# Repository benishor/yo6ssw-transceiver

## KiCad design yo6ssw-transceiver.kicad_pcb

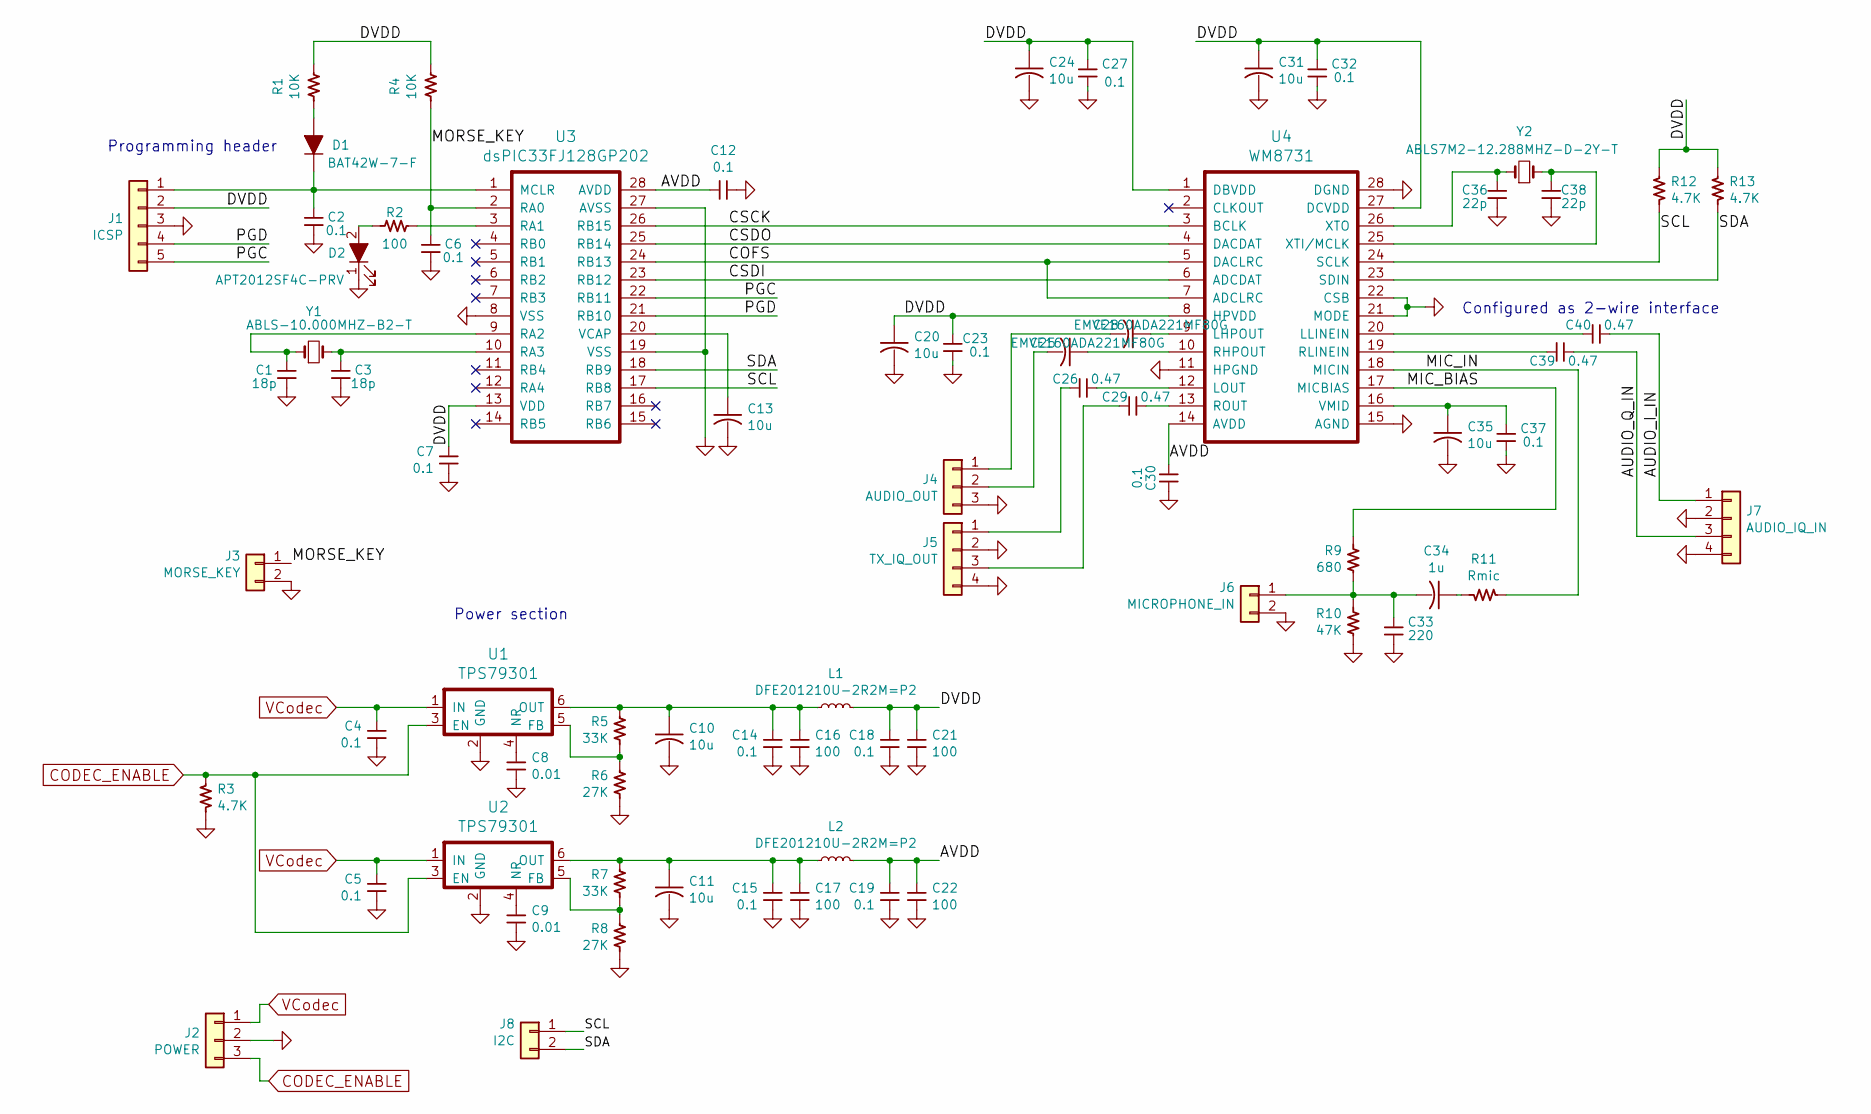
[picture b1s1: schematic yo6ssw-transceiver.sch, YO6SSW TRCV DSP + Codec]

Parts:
C1, C3: 18p; C_0805_2012Metric_Pad1.15x1.50mm_HandSolder
C2, C4, C5, C6, C7, C12, C14, C15, C18, C19, C23, C27, C30, C32, C37: 0.1; C_0805_2012Metric_Pad1.15x1.50mm_HandSolder
C8, C9: 0.01; C_0805_2012Metric_Pad1.15x1.50mm_HandSolder
C10, C11, C13, C20, C24, C31, C35: 10u; C_0805_2012Metric_Pad1.15x1.50mm_HandSolder
C16, C17, C21, C22: 100; C_0805_2012Metric_Pad1.15x1.50mm_HandSolder
C25, C28: EMVE160ADA221MF80G; CP_Elec_6.3x7.7
C26, C29, C39, C40: 0.47; C_0805_2012Metric_Pad1.15x1.50mm_HandSolder
C33: 220; C_0805_2012Metric_Pad1.15x1.50mm_HandSolder
C34: 1u; C_0805_2012Metric_Pad1.15x1.50mm_HandSolder
C36, C38: 22p; C_0805_2012Metric_Pad1.15x1.50mm_HandSolder
D1: BAT42W-7-F; D_SOD-123
D2: APT2012SF4C-PRV; D_0805_2012Metric_Pad0.97x1.50mm_HandSolder
J1: ICSP; PinSocket_1x05_P2.54mm_Vertical_SMD_Pin1Left
J2: POWER; PinSocket_1x03_P2.54mm_Vertical_SMD_Pin1Left
J3: MORSE_KEY; PinSocket_1x02_P2.54mm_Vertical_SMD_Pin1Left
J4: AUDIO_OUT; PinSocket_1x03_P2.54mm_Vertical_SMD_Pin1Left
J5: TX_IQ_OUT; PinSocket_1x04_P2.54mm_Vertical_SMD_Pin1Left
J6: MICROPHONE_IN; PinSocket_1x02_P2.54mm_Vertical_SMD_Pin1Left
J7: AUDIO_IQ_IN; PinSocket_1x04_P2.54mm_Vertical_SMD_Pin1Left
J8: I2C; PinSocket_1x02_P2.54mm_Vertical_SMD_Pin1Left
L1, L2: DFE201210U-2R2M=P2; L_0805_2012Metric_Pad1.15x1.50mm_HandSolder
R1, R4: 10K; R_0805_2012Metric_Pad1.15x1.50mm_HandSolder
R2: 100; R_0805_2012Metric_Pad1.15x1.50mm_HandSolder
R3, R12, R13: 4.7K; R_0805_2012Metric_Pad1.15x1.50mm_HandSolder
R5, R7: 33K; R_0805_2012Metric_Pad1.15x1.50mm_HandSolder
R6, R8: 27K; R_0805_2012Metric_Pad1.15x1.50mm_HandSolder
R9: 680; R_0805_2012Metric_Pad1.15x1.50mm_HandSolder
R10: 47K; R_0805_2012Metric_Pad1.15x1.50mm_HandSolder
R11: Rmic; R_0805_2012Metric_Pad1.15x1.50mm_HandSolder
U1, U2: TPS79301; SOT-23-6_Handsoldering
U3: dsPIC33FJ128GP202; SOIC-28W_7.5x17.9mm_P1.27mm
U4: WM8731; SSOP-28_5.3x10.2mm_P0.65mm
Y1: ABLS-10.000MHZ-B2-T; Crystal_SMD_HC49-SD_HandSoldering
Y2: ABLS7M2-12.288MHZ-D-2Y-T; Crystal_SMD_HC49-SD_HandSoldering

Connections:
/AUDIO_I_IN: C40.2, J7.1
/AUDIO_Q_IN: C39.2, J7.3
/AVDD: C12.2, C19.1, C22.1, C30.1, L2.2, U3.28 (AVDD), U4.14 (AVDD)
/COFS: U3.24 (RB13), U4.5 (DACLRC), U4.7 (ADCLRC)
/CSCK: U3.26 (RB15), U4.3 (BCLK)
/CSDI: U3.23 (RB12), U4.6 (ADCDAT)
/CSDO: U3.25 (RB14), U4.4 (DACDAT)
/DVDD: C7.1, C18.1, C20.1, C21.1, C23.2, C24.1, C27.2, C31.1, C32.2, J1.2, L1.2, R1.1, R4.1, R12.1, R13.1, U3.13 (VDD), U4.1 (DBVDD), U4.8 (HPVDD), U4.27 (DCVDD)
/MIC_BIAS: R9.2, U4.17 (MICBIAS)
/MIC_IN: R11.1, U4.18 (MICIN)
/MORSE_KEY: C6.2, J3.1, R4.2, U3.2 (RA0)
/PGC: J1.5, U3.22 (RB11)
/PGD: J1.4, U3.21 (RB10)
/SCL: J8.1, R12.2, U3.17 (RB8), U4.24 (SCLK)
/SDA: J8.2, R13.2, U3.18 (RB9), U4.23 (SDIN)
CODEC_ENABLE: J2.3, R3.1, U1.3 (EN), U2.3 (EN)
GND: C1.1, C2.1, C3.1, C4.2, C5.2, C6.1, C7.2, C8.2, C9.2, C10.2, C11.2, C12.1, C13.2, C14.2, C15.2, C16.2, C17.2, C18.2, C19.2, C20.2, C21.2, C22.2, C23.1, C24.2, C27.1, C30.2, C31.2, C32.1, C33.1, C35.2, C36.1, C37.1, C38.1, D2.1 (K), J1.3, J2.2, J3.2, J4.3, J5.2, J5.4, J6.2, J7.2, J7.4, R3.2, R6.2, R8.2, R10.1, U1.2 (GND), U2.2 (GND), U3.8 (VSS), U3.19 (VSS), U3.27 (AVSS), U4.11 (HPGND), U4.15 (AGND), U4.21 (MODE), U4.22 (CSB), U4.28 (DGND)
unnamed: C1.2, U3.9 (RA2), Y1.1
unnamed: C2.2, D1.1 (K), J1.1, U3.1 (MCLR)
unnamed: C3.2, U3.10 (RA3), Y1.2
unnamed: C8.1, U1.4 (NR)
unnamed: C9.1, U2.4 (NR)
unnamed: C10.1, C14.1, C16.1, L1.1, R5.1, U1.6 (OUT)
unnamed: C11.1, C15.1, C17.1, L2.1, R7.1, U2.6 (OUT)
unnamed: C13.1, U3.20 (VCAP)
unnamed: C25.1, U4.10 (RHPOUT)
unnamed: C25.2, J4.2
unnamed: C26.1, J5.1
unnamed: C26.2, U4.12 (LOUT)
unnamed: C28.1, U4.9 (LHPOUT)
unnamed: C28.2, J4.1
unnamed: C29.1, J5.3
unnamed: C29.2, U4.13 (ROUT)
unnamed: C33.2, C34.2, J6.1, R9.1, R10.2
unnamed: C34.1, R11.2
unnamed: C35.1, C37.2, U4.16 (VMID)
unnamed: C36.2, U4.26 (XTO), Y2.1
unnamed: C38.2, U4.25 (XTI/MCLK), Y2.2
unnamed: C39.1, U4.19 (RLINEIN)
unnamed: C40.1, U4.20 (LLINEIN)
unnamed: D1.2 (A), R1.2
unnamed: D2.2 (A), R2.2
unnamed: R2.1, U3.3 (RA1)
unnamed: R5.2, R6.1, U1.5 (FB)
unnamed: R7.2, R8.1, U2.5 (FB)
VCodec: C4.1, C5.1, J2.1, U1.1 (IN), U2.1 (IN)

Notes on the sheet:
Configured as 2-wire interface
Programming header
Power section

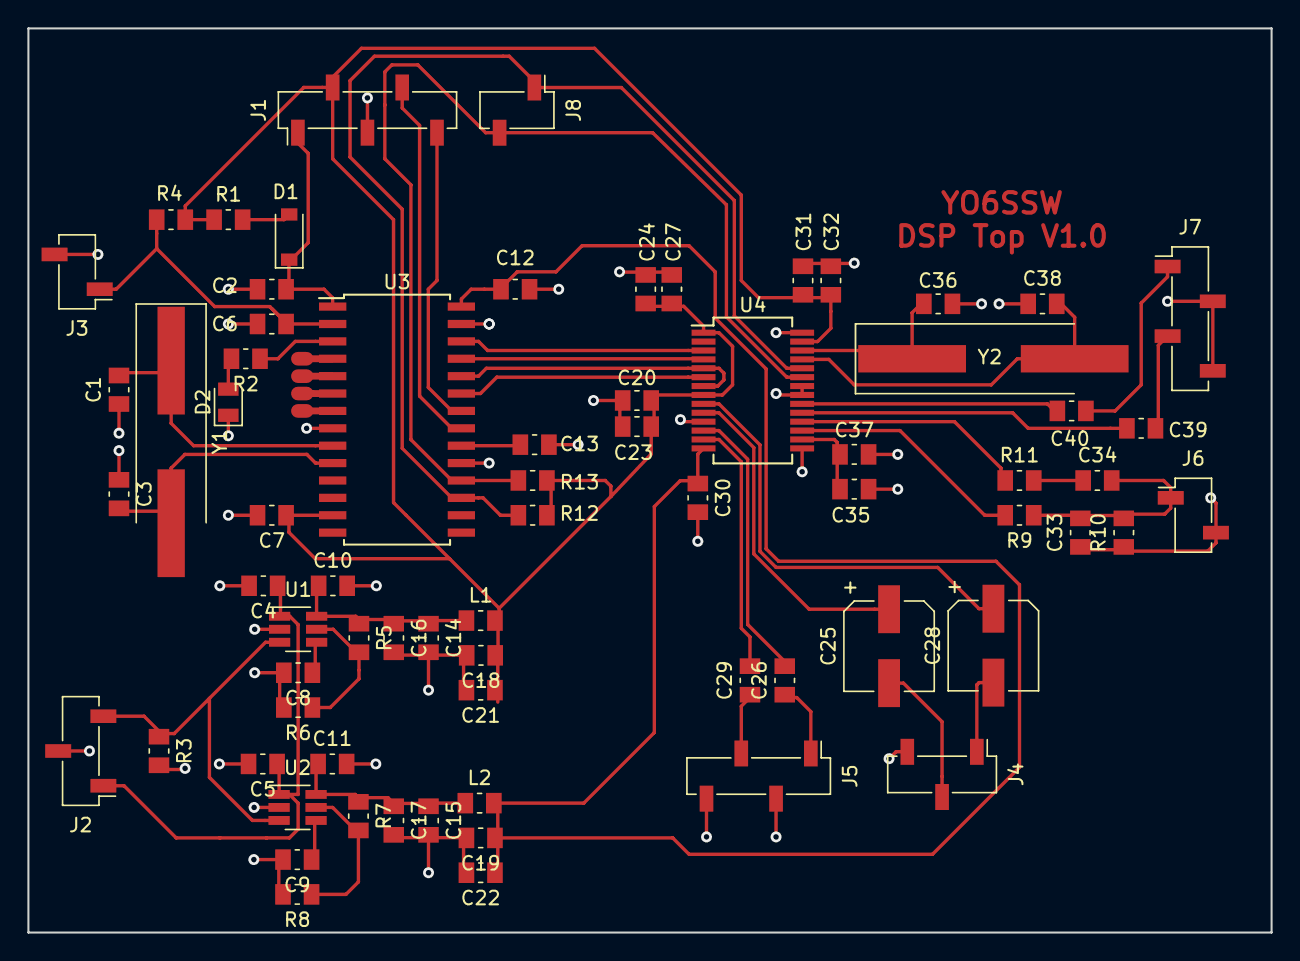
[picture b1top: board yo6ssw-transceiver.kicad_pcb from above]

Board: 2 copper layers, 90.8 x 66.0 mm, 71 parts (0 on the bottom side), 46 nets.

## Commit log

2017-10-10 Added DSP + audio codec module schematic and PCB v1
2018-04-14 Backup before changing pin headers
